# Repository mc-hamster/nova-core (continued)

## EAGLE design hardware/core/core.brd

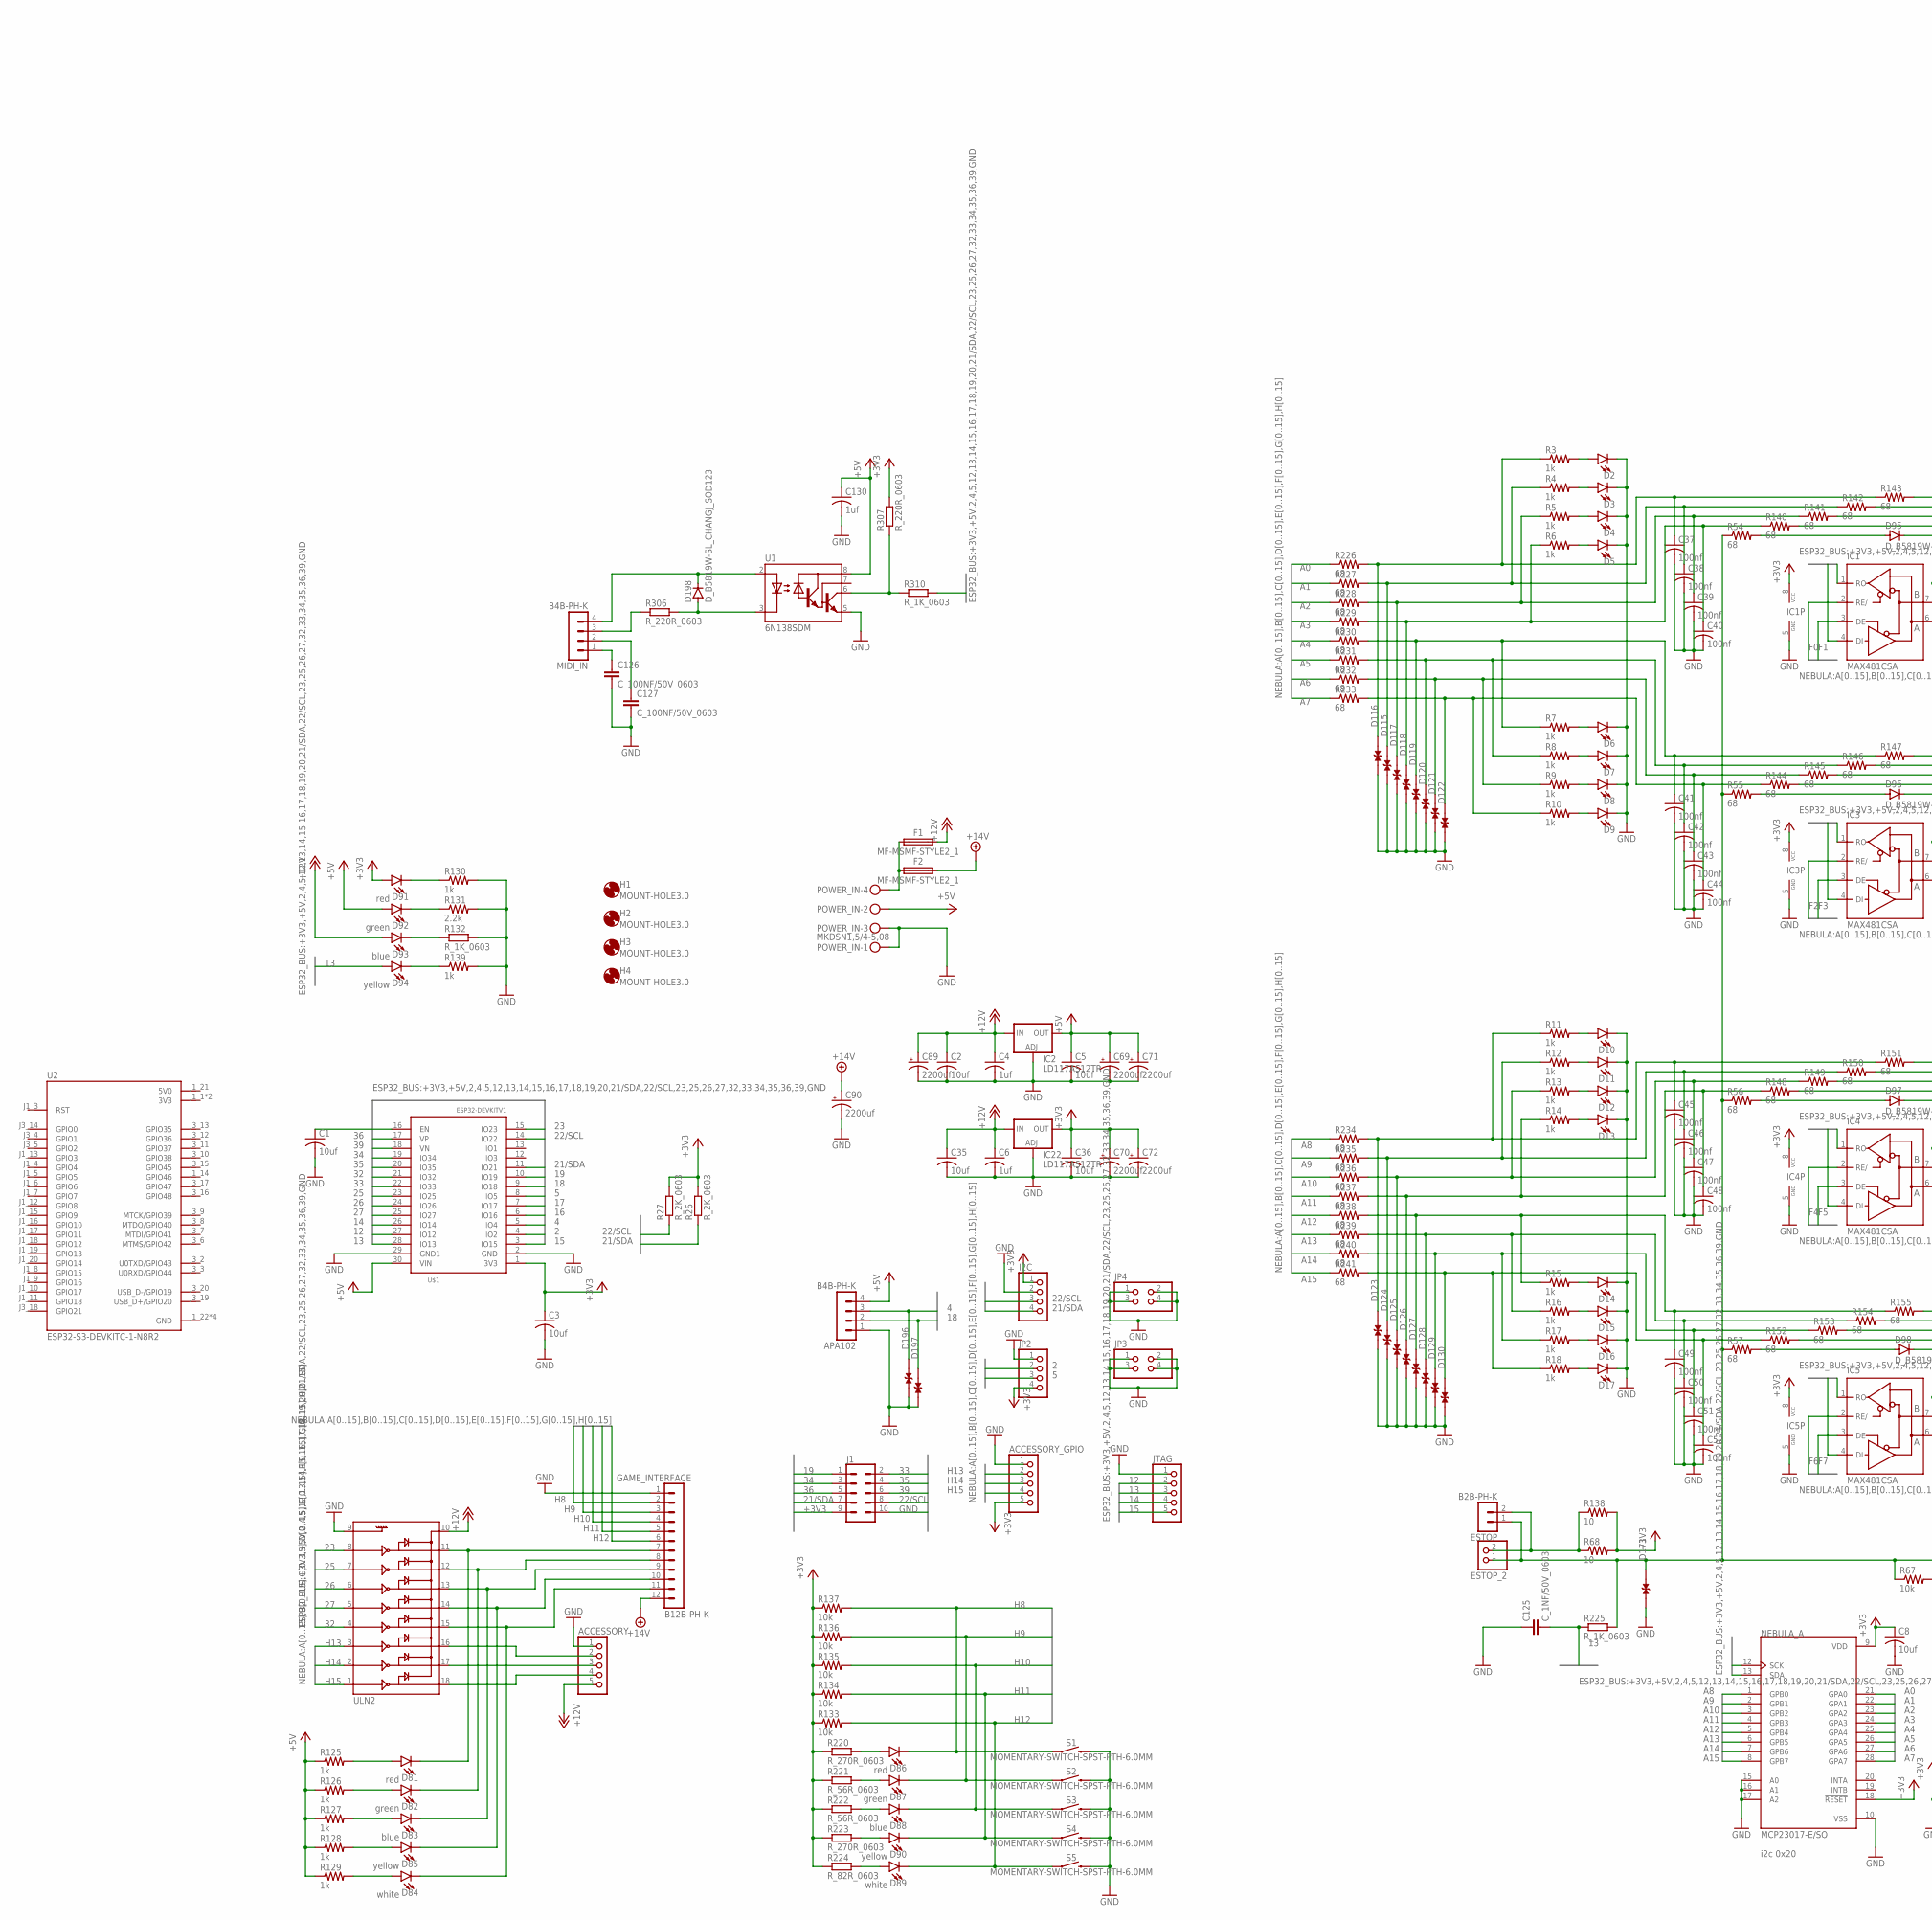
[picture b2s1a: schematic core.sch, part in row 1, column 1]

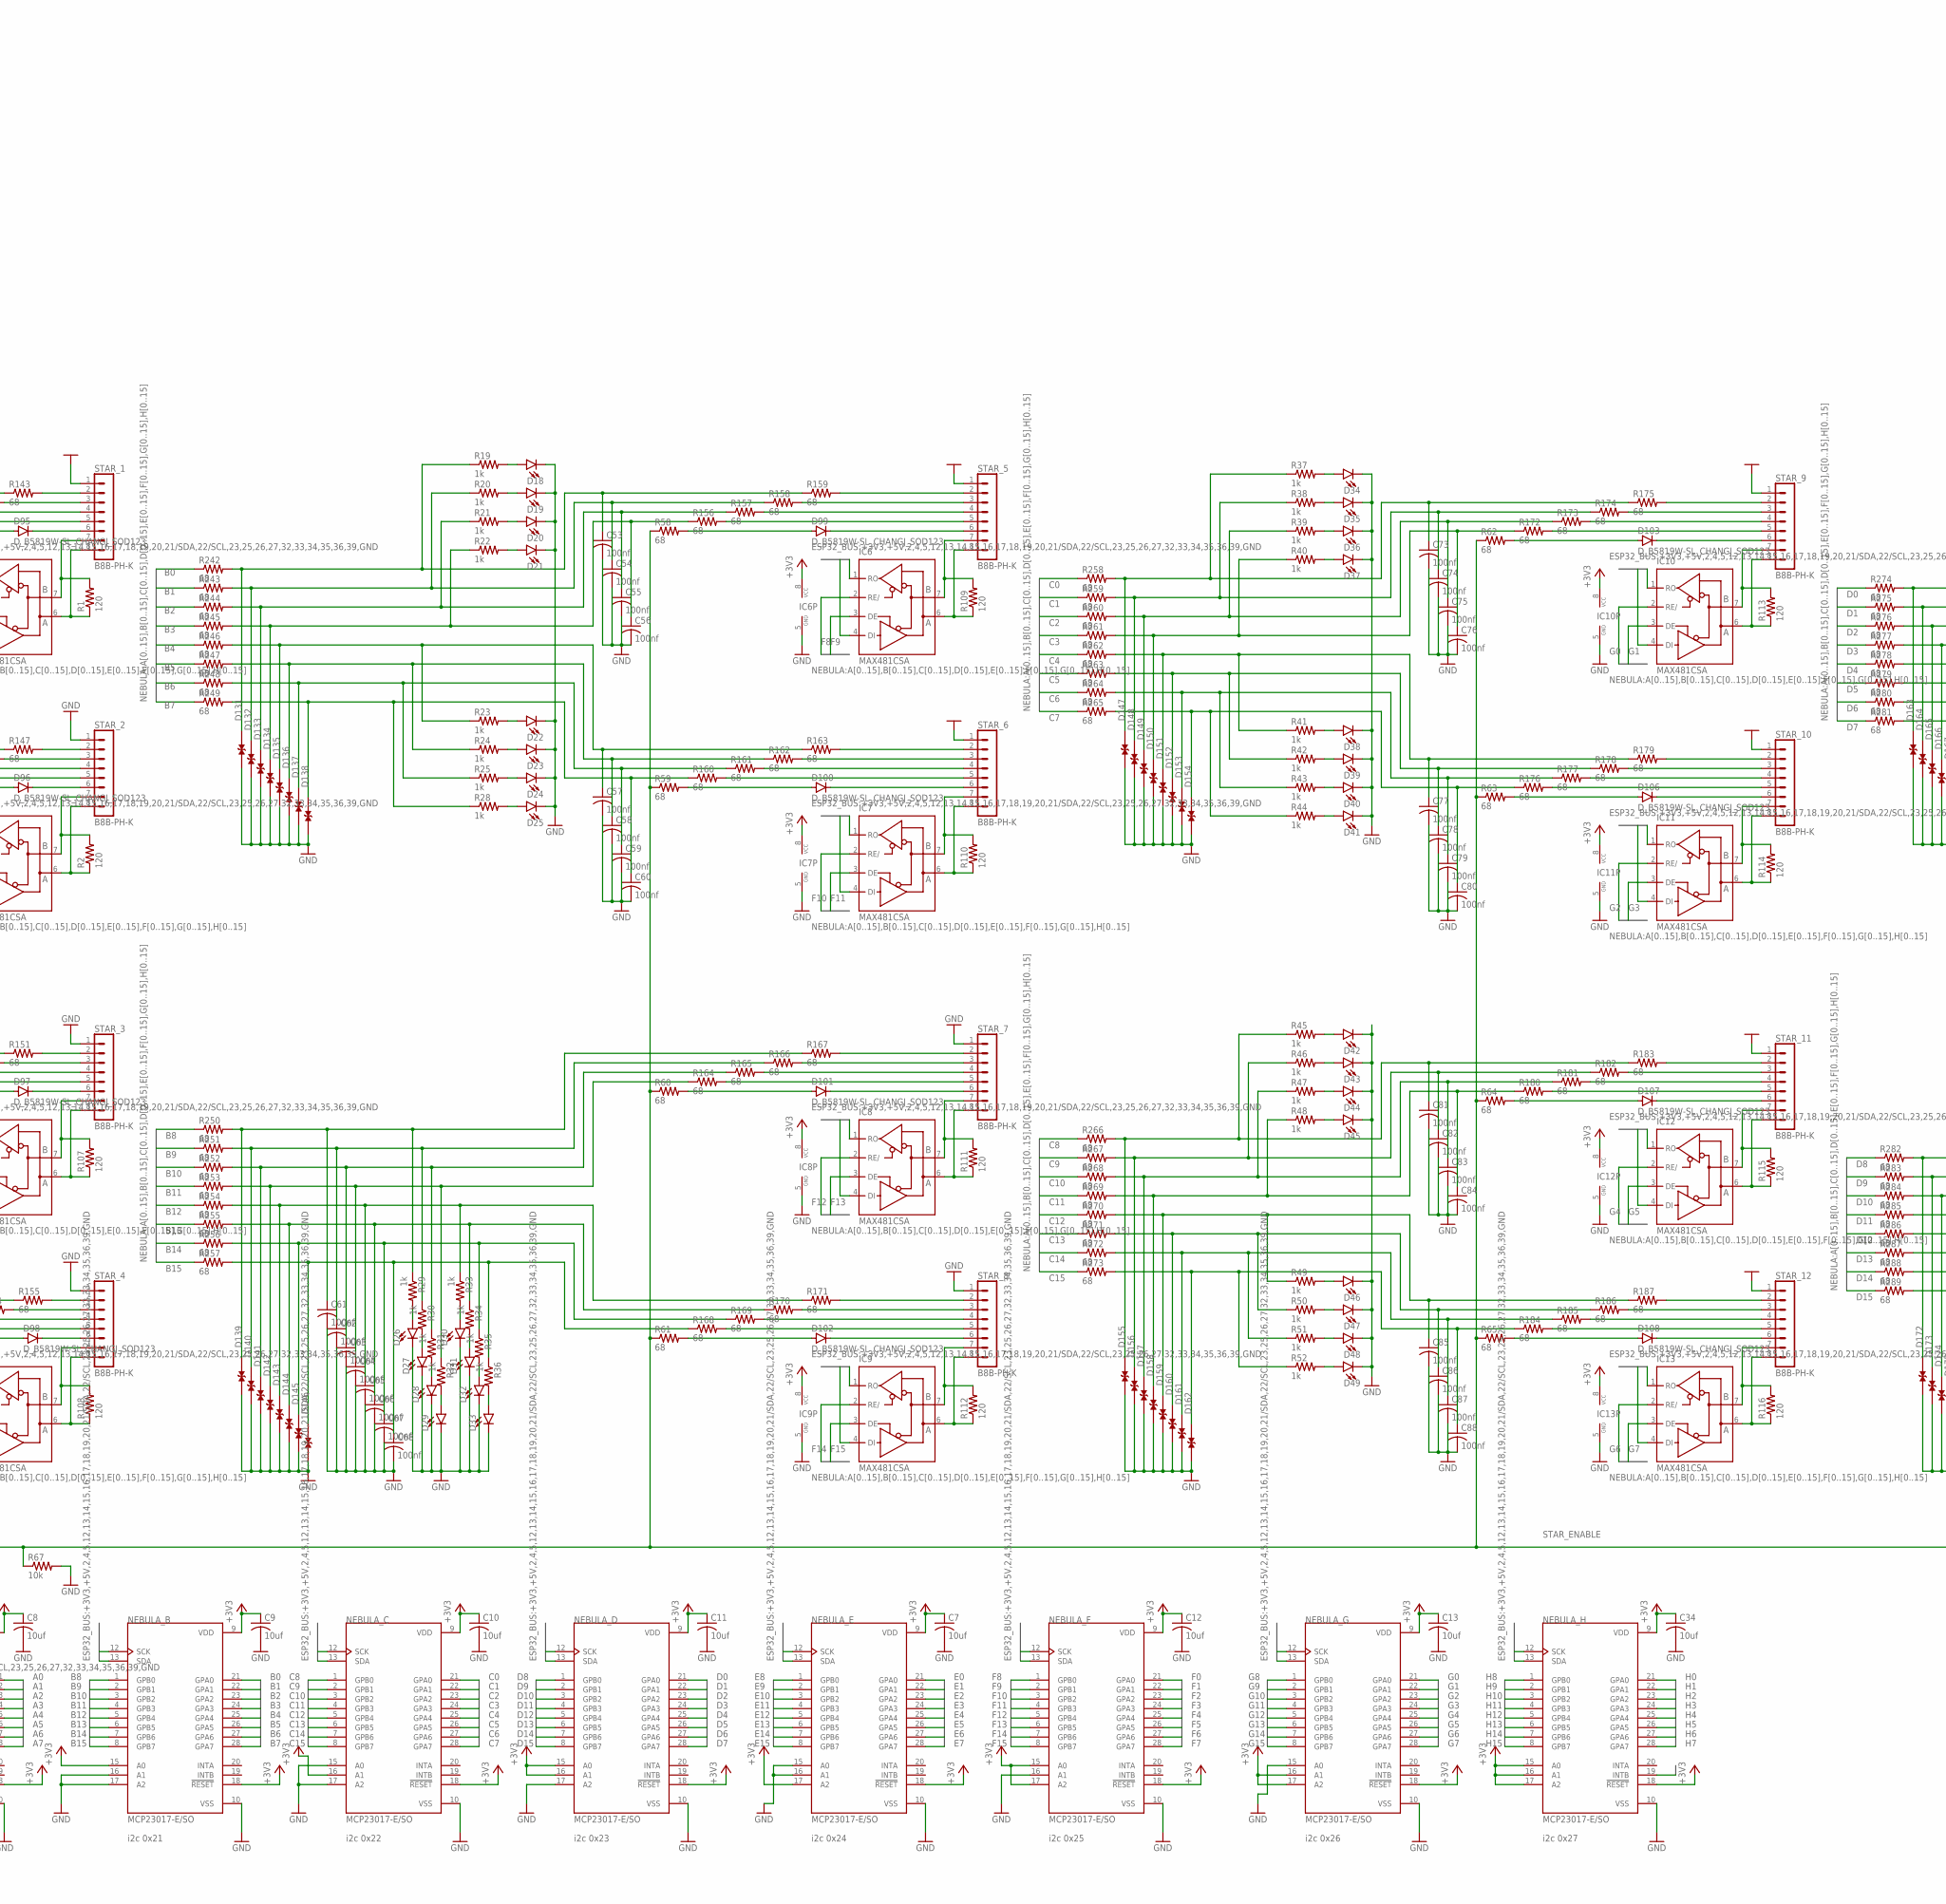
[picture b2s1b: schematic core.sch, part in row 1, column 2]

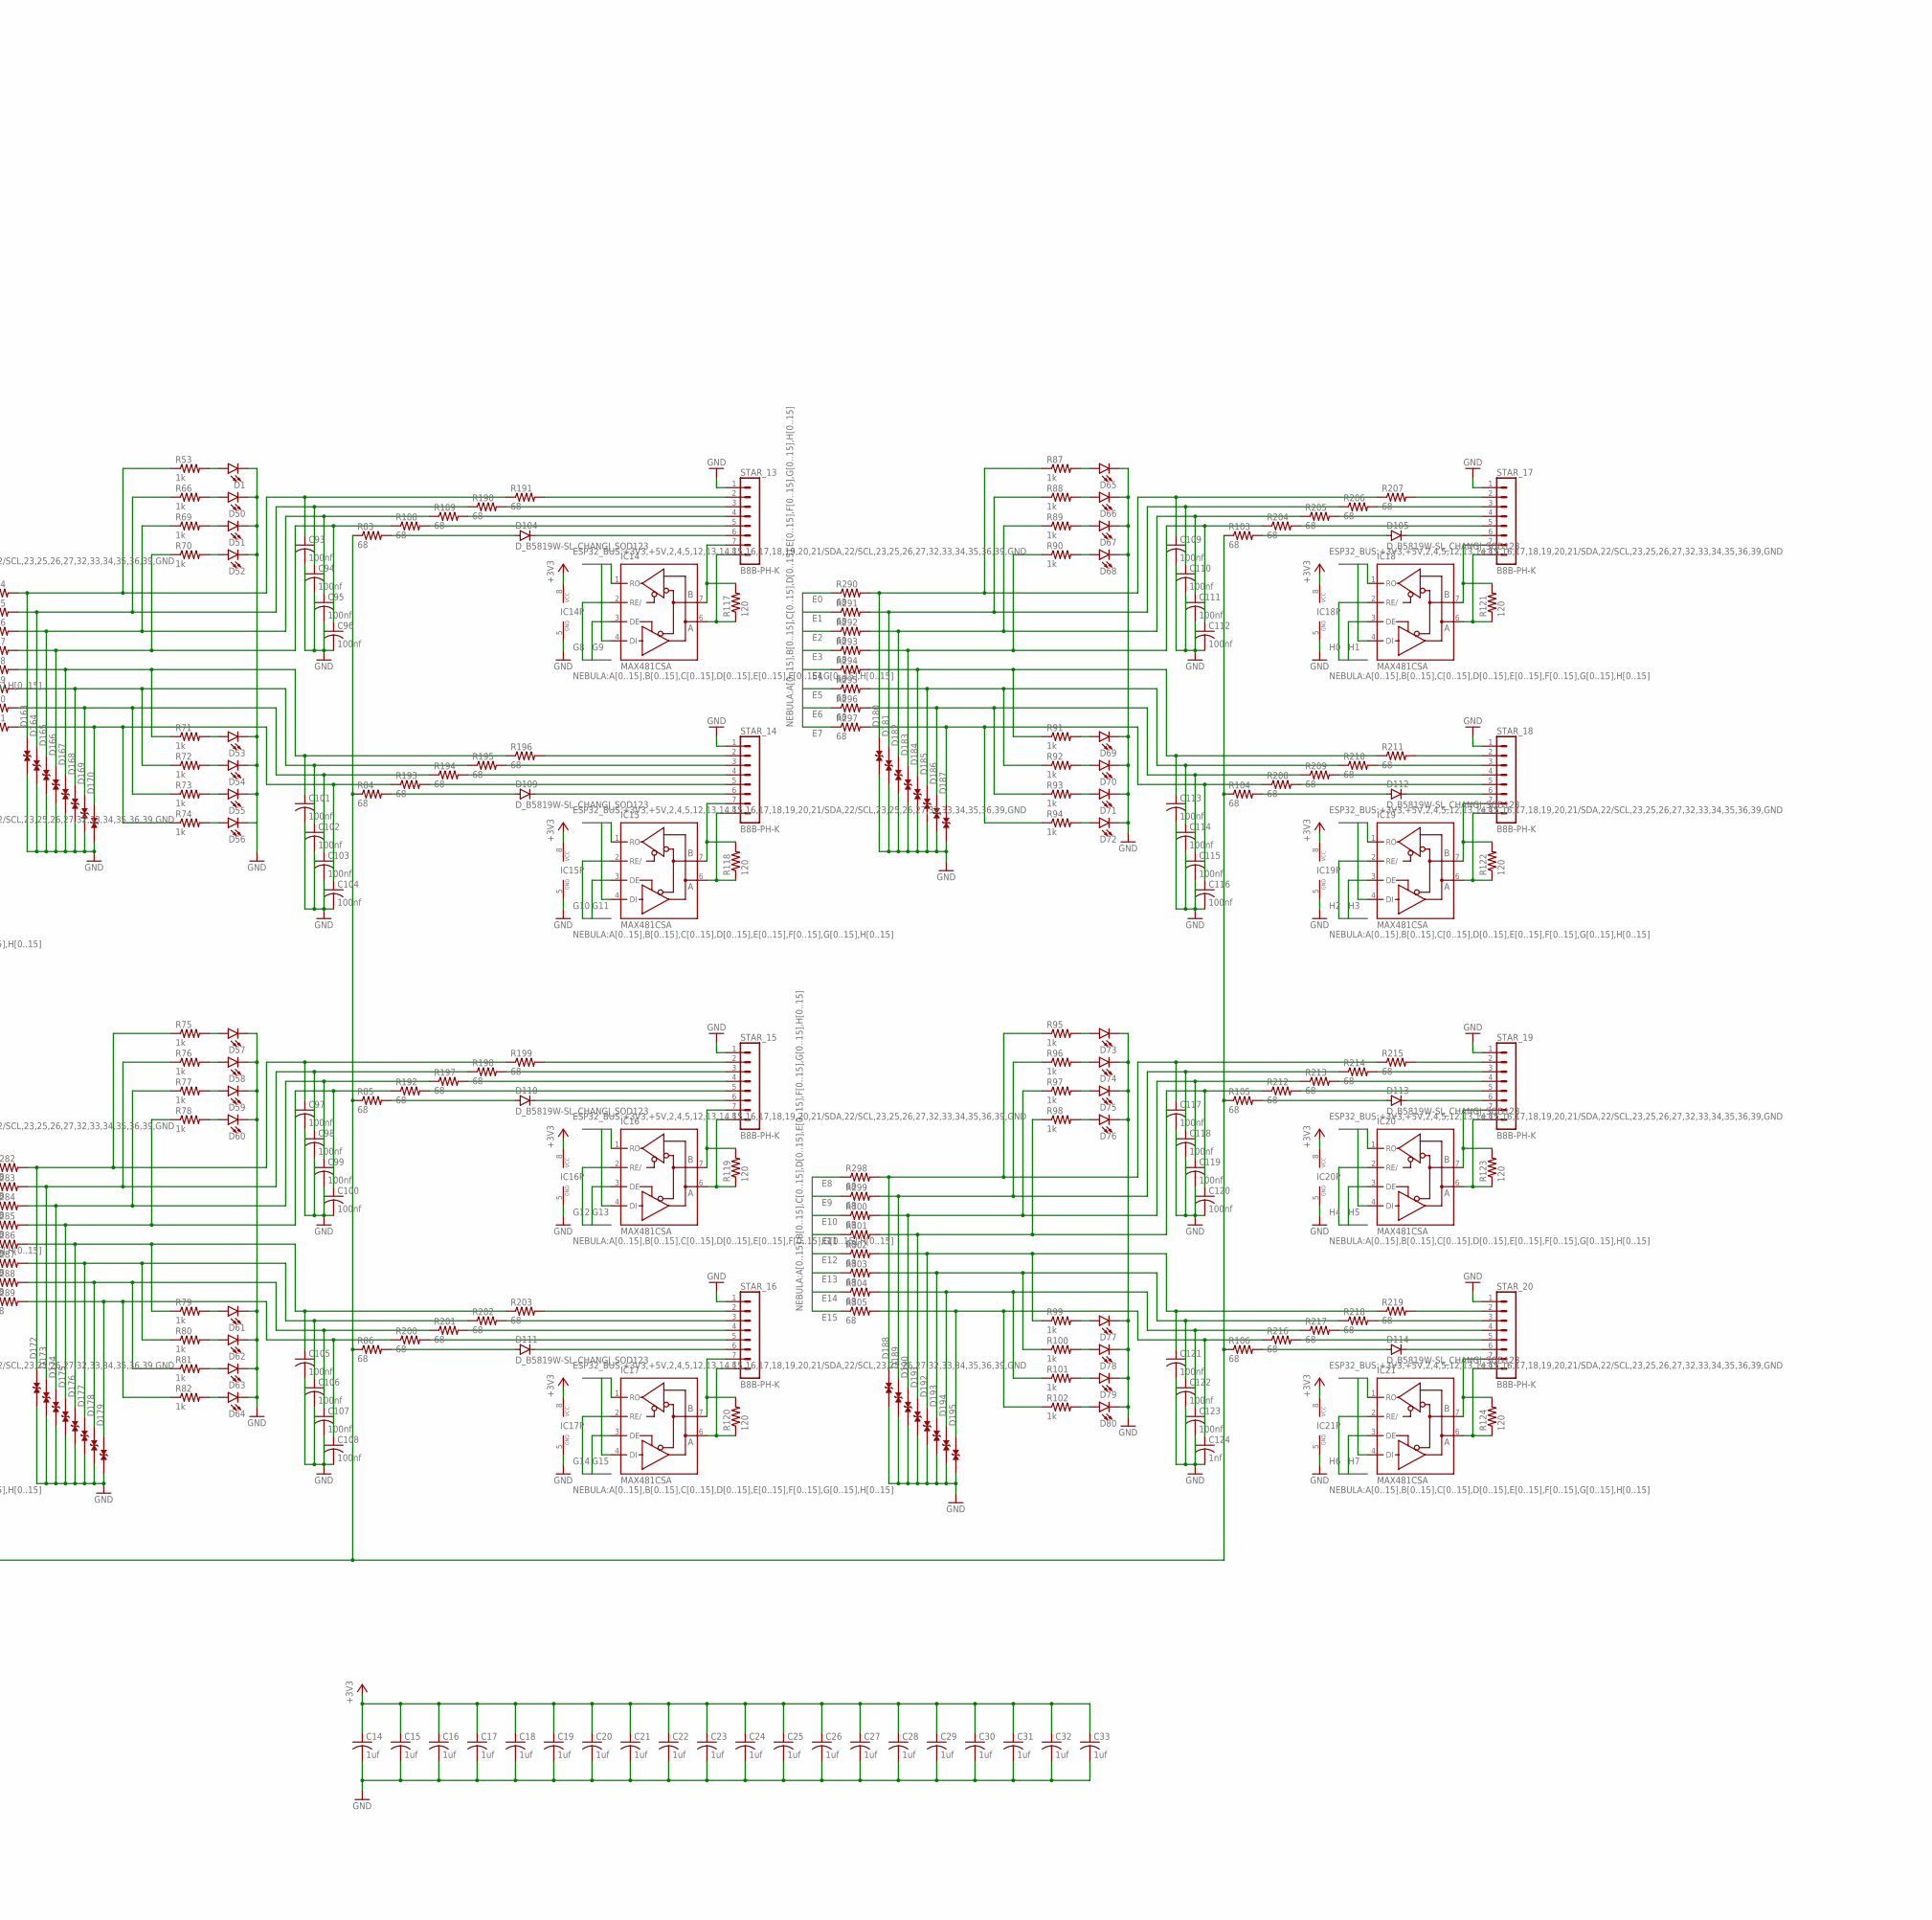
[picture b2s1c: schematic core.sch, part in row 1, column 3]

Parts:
ACCESSORY: PINHD-1X5; 1X05
ACCESSORY_GPIO: PINHD-1X5; 1X05
APA102: B4B-PH-K
C1, C2, C3, C5, C7, C8, C9, C10, C11, C12, C13, C34, C35, C36: 10uf; C0603; LCSC_PART C19702
C4, C6, C14, C15, C16, C17, C18, C19, C20, C21, C22, C23, C24, C25, C26, C27, C28, C29, C30, C31, C32, C33, C130: 1uf; C0805; LCSC_PART C15849
C37, C38, C39, C40, C41, C42, C43, C44, C45, C46, C47, C48, C49, C50, C51, C52, C53, C54, C55, C56, C57, C58, C59, C60, C61, C62, C63, C64, C65, C66, C67, C68, C73, C74, C75, C76, C77, C78, C79, C80, C81, C82, C83, C84, C85, C86, C87, C88, C93, C94, C95, C96, C97, C98, C99, C100, C101, C102, C103, C104, C105, C106, C107, C108, C109, C110, C111, C112, C113, C114, C115, C116, C117, C118, C119, C120, C121, C122, C123: 100nf; C0603; LCSC_PART C14663
C69, C70, C71, C72, C89, C90: 2200uf; E5-13
C124: 1nf; C0603; LCSC_PART C1588
C125: C_1NF/50V_0603; C0603
C126, C127: C_100NF/50V_0603; C0603
D1, D2, D6, D10, D14, D18, D22, D26, D30, D34, D38, D42, D46, D53, D57, D61, D65, D69, D73, D77: LED0603; LED-0603; LCSC_PART C2286
D3, D7, D11, D15, D19, D23, D27, D31, D35, D39, D43, D47, D50, D54, D58, D62, D66, D70, D74, D78: LED0603; LED-0603; LCSC_PART C72043
D4, D8, D12, D16, D20, D24, D28, D32, D36, D40, D44, D48, D51, D55, D59, D63, D67, D71, D75, D79: LED0603; LED-0603; LCSC_PART C72041
D5, D9, D13, D17, D21, D25, D29, D33, D37, D41, D45, D49, D52, D56, D60, D64, D68, D72, D76, D80: LED0603; LED-0603; LCSC_PART C2290
D81, D86, D91: red; LED-0603; LCSC_PART C2286
D82, D87, D92: green; LED-0603; LCSC_PART C72043
D83, D88, D93: blue; LED-0603; LCSC_PART C72041
D84, D89: white; LED-0603; LCSC_PART C2290
D85, D90, D94: yellow; LED-0603; LCSC_PART C72038
D95, D96, D97, D98, D99, D100, D101, D102, D103, D104, D105, D106, D107, D108, D109, D110, D111, D112, D113, D114, D198: D_B5819W-SL_CHANGJ_SOD123; SOD123
D115, D116, D117, D118, D119, D120, D121, D122, D123, D124, D125, D126, D127, D128, D129, D130, D131, D132, D133, D134, D135, D136, D137, D138, D139, D140, D141, D142, D143, D144, D145, D146, D147, D148, D149, D150, D151, D152, D153, D154, D155, D156, D157, D158, D159, D160, D161, D162, D163, D164, D165, D166, D167, D168, D169, D170, D171, D172, D173, D174, D175, D176, D177, D178, D179, D180, D181, D182, D183, D184, D185, D186, D187, D188, D189, D190, D191, D192, D193, D194, D195, D196, D197: SMBJ8.0CA; DIOM4336X265N; LCSC_PART C78757
ESTOP: B2B-PH-K
ESTOP_2: PINHD-1X2; 1X02
F1, F2: MF-MSMF-STYLE2_1; FUSC4632X160; LCSC_PART C78695
GAME_INTERFACE: B12B-PH-K
H1, H2, H3, H4: MOUNT-HOLE3.0; 3,0
I2C: PINHD-1X4; 1X04
IC1, IC3, IC4, IC5, IC6, IC7, IC8, IC9, IC10, IC11, IC12, IC13, IC14, IC15, IC16, IC17, IC18, IC19, IC20, IC21: MAX481CSA; SO08; LCSC_PART C8963
IC2: LD117AS12TR; SOT223; LCSC_PART C6187
IC22: LD117AS12TR; SOT223; LCSC_PART C347222
J1: CONN_05X2SHD; 2X5-SHROUDED
JP2: PINHD-1X4; 1X04
JP3, JP4: PINHD-2X2; 2X02
JTAG: PINHD-1X5; 1X05
MIDI_IN: B4B-PH-K
NEBULA_A: MCP23017-E/SO; SOIC127P1030X265-28N; LCSC_PART C629440
NEBULA_B: MCP23017-E/SO; SOIC127P1030X265-28N; LCSC_PART C629440
NEBULA_C: MCP23017-E/SO; SOIC127P1030X265-28N; LCSC_PART C629440
NEBULA_D: MCP23017-E/SO; SOIC127P1030X265-28N; LCSC_PART C629440
NEBULA_E: MCP23017-E/SO; SOIC127P1030X265-28N; LCSC_PART C629440
NEBULA_F: MCP23017-E/SO; SOIC127P1030X265-28N; LCSC_PART C629440
NEBULA_G: MCP23017-E/SO; SOIC127P1030X265-28N; LCSC_PART C629440
NEBULA_H: MCP23017-E/SO; SOIC127P1030X265-28N; LCSC_PART C629440
POWER_IN: MKDSN1,5/4-5,08
R1, R2, R107, R108, R109, R110, R111, R112, R113, R114, R115, R116, R117, R118, R119, R120, R121, R122, R123, R124: 120; R0603; LCSC_PART C22787
R3, R4, R5, R6, R7, R8, R9, R10, R11, R12, R13, R14, R15, R16, R17, R18, R19, R20, R21, R22, R23, R24, R25, R28, R29, R30, R31, R32, R33, R34, R35, R36, R37, R38, R39, R40, R41, R42, R43, R44, R45, R46, R47, R48, R49, R50, R51, R52, R53, R66, R69, R70, R71, R72, R73, R74, R75, R76, R77, R78, R79, R80, R81, R82, R87, R88, R89, R90, R91, R92, R93, R94, R95, R96, R97, R98, R99, R100, R101, R102, R125, R126, R127, R128, R129, R130, R139: 1k; R0603; LCSC_PART C21190
R26, R27: R_2K_0603; R0603
R54, R55, R56, R57, R58, R59, R60, R61, R62, R63, R64, R65, R83, R84, R85, R86, R103, R104, R105, R106, R140, R141, R142, R143, R144, R145, R146, R147, R148, R149, R150, R151, R152, R153, R154, R155, R156, R157, R158, R159, R160, R161, R162, R163, R164, R165, R166, R167, R168, R169, R170, R171, R172, R173, R174, R175, R176, R177, R178, R179, R180, R181, R182, R183, R184, R185, R186, R187, R188, R189, R190, R191, R192, R193, R194, R195, R196, R197, R198, R199, R200, R201, R202, R203, R204, R205, R206, R207, R208, R209, R210, R211, R212, R213, R214, R215, R216, R217, R218, R219, R226, R227, R228, R229, R230, R231, R232, R233, R234, R235, R236, R237, R238, R239, R240, R241, R242, R243, R244, R245, R246, R247, R248, R249, R250, R251, R252, R253, R254, R255, R256, R257, R258, R259, R260, R261, R262, R263, R264, R265, R266, R267, R268, R269, R270, R271, R272, R273, R274, R275, R276, R277, R278, R279, R280, R281, R282, R283, R284, R285, R286, R287, R288, R289, R290, R291, R292, R293, R294, R295, R296, R297, R298, R299, R300, R301, R302, R303, R304, R305: 68; R0603; LCSC_PART c27592
R67, R133, R134, R135, R136, R137: 10k; R0603; LCSC_PART C25804
R68, R138: 10; R1206; LCSC_PART C17903
R131: 2.2k; R0603; LCSC_PART C4190
R132, R225, R310: R_1K_0603; R0603
R220, R223: R_270R_0603; R0603
R221, R222: R_56R_0603; R0603
R224: R_82R_0603; R0603
R306, R307: R_220R_0603; R0603
S1, S2, S3, S4, S5: MOMENTARY-SWITCH-SPST-PTH-6.0MM; TACTILE_SWITCH_PTH_6.0MM
STAR_1, STAR_2, STAR_3, STAR_4, STAR_5, STAR_6, STAR_7, STAR_8, STAR_9, STAR_10, STAR_11, STAR_12, STAR_13, STAR_14, STAR_15, STAR_16, STAR_17, STAR_18, STAR_19, STAR_20: B8B-PH-K
U1: 6N138SDM; COUPL_6N138SDM; LCSC_PART C188666
U2: ESP32-S3-DEVKITC-1-N8R2; XCVR_ESP32-S3-DEVKITC-1-N8R2
U$1: ESP32DEVKITV1; ESP32-DEVKITV1
ULN2: ULN2803SOICW; SO18L

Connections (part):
2: JP2.2, U$1.4 (IO2)
4: APA102.3, D196.2, U$1.5 (IO4)
5: JP2.3, U$1.8 (IO5)
12: JTAG.2, U$1.27 (IO12)
13: C125.2, D94.A, JTAG.3, R225.1, U$1.28 (IO13)
14: JTAG.4, U$1.26 (IO14)
15: JTAG.5, U$1.3 (IO15)
16/RX2: IC1.1 (RO), IC3.1 (RO), IC4.1 (RO), IC5.1 (RO), IC6.1 (RO), IC7.1 (RO), IC8.1 (RO), IC9.1 (RO), IC10.1 (RO), IC11.1 (RO), IC12.1 (RO), IC13.1 (RO), IC14.1 (RO), IC15.1 (RO), IC16.1 (RO), IC17.1 (RO), IC18.1 (RO), IC19.1 (RO), IC20.1 (RO), IC21.1 (RO), U$1.6 (IO16); also elsewhere on the board
17/TX2: IC1.4 (DI), IC3.4 (DI), IC4.4 (DI), IC5.4 (DI), IC6.4 (DI), IC7.4 (DI), IC8.4 (DI), IC9.4 (DI), IC10.4 (DI), IC11.4 (DI), IC12.4 (DI), IC13.4 (DI), IC14.4 (DI), IC15.4 (DI), IC16.4 (DI), IC17.4 (DI), IC18.4 (DI), IC19.4 (DI), IC20.4 (DI), IC21.4 (DI), U$1.7 (IO17); also elsewhere on the board
18: APA102.2, D197.2, U$1.9 (IO18)
19: J1.1, R307.1, R310.1, R310.2, U1.6 (VO), U$1.10 (IO19)
21/SDA: I2C.4, J1.7, NEBULA_A.13 (SDA), NEBULA_B.13 (SDA), NEBULA_C.13 (SDA), NEBULA_D.13 (SDA), NEBULA_E.13 (SDA), NEBULA_F.13 (SDA), NEBULA_G.13 (SDA), NEBULA_H.13 (SDA), R26.1, U$1.11 (IO21)
22/SCL: I2C.3, J1.8, NEBULA_A.12 (SCK), NEBULA_B.12 (SCK), NEBULA_C.12 (SCK), NEBULA_D.12 (SCK), NEBULA_E.12 (SCK), NEBULA_F.12 (SCK), NEBULA_G.12 (SCK), NEBULA_H.12 (SCK), R27.1, U$1.14 (IO22)
23: U$1.15 (IO23), ULN2.8
25: U$1.23 (IO25), ULN2.7
26: U$1.24 (IO26), ULN2.6
27: U$1.25 (IO27), ULN2.5
32: U$1.21 (IO32), ULN2.4
33: J1.2, U$1.22 (IO33)
34: J1.3, U$1.19 (IO34)
35: J1.4, U$1.20 (IO35)
36: J1.5, U$1.17 (VP)
39: J1.6, NEBULA_H.19 (INTB), U$1.18 (VN)
+3V3: ACCESSORY_GPIO.5, C3.1, C7.1, C8.1, C9.1, C10.1, C11.1, C12.1, C13.1, C14.1, C15.1, C16.1, C17.1, C18.1, C19.1, C20.1, C21.1, C22.1, C23.1, C24.1, C25.1, C26.1, C27.1, C28.1, C29.1, C30.1, C31.1, C32.1, C33.1, C34.1, C36.1, C70.+, C72.+, D91.A, I2C.1, IC1.8 (VCC), IC3.8 (VCC), IC4.8 (VCC), IC5.8 (VCC), IC6.8 (VCC), IC7.8 (VCC), IC8.8 (VCC), IC9.8 (VCC), IC10.8 (VCC), IC11.8 (VCC), IC12.8 (VCC), IC13.8 (VCC), IC14.8 (VCC), IC15.8 (VCC), IC16.8 (VCC), IC17.8 (VCC), IC18.8 (VCC), IC19.8 (VCC), IC20.8 (VCC), IC21.8 (VCC), IC22.4 (OUT), J1.9, JP2.4, NEBULA_A.9 (VDD), NEBULA_A.18 (!RESET), NEBULA_B.9 (VDD), NEBULA_B.15 (A0), NEBULA_B.18 (!RESET), NEBULA_C.9 (VDD), NEBULA_C.16 (A1), NEBULA_C.18 (!RESET), NEBULA_D.9 (VDD), NEBULA_D.15 (A0), NEBULA_D.16 (A1), NEBULA_D.18 (!RESET), NEBULA_E.9 (VDD), NEBULA_E.17 (A2), NEBULA_E.18 (!RESET), NEBULA_F.9 (VDD), NEBULA_F.15 (A0), NEBULA_F.17 (A2), NEBULA_F.18 (!RESET), NEBULA_G.9 (VDD), NEBULA_G.16 (A1), NEBULA_G.17 (A2)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
+5V: APA102.4, C5.1, C69.+, C71.+, C130.1, D92.A, IC2.4 (OUT), POWER_IN.2, R125.1, R126.1, R127.1, R128.1, R129.1, U1.8 (VCC), U$1.30 (VIN)
+12V: ACCESSORY.5, C2.1, C4.1, C6.1, C35.1, C89.+, D93.A, F1.2, IC2.3 (IN), IC22.3 (IN), ULN2.10
+14V: C90.+, F2.2, GAME_INTERFACE.12
A0: NEBULA_A.21 (GPA0), R226.1
A1: NEBULA_A.22 (GPA1), R227.1
A2: NEBULA_A.23 (GPA2), R228.1
A3: NEBULA_A.24 (GPA3), R229.1
A4: NEBULA_A.25 (GPA4), R230.1
A5: NEBULA_A.26 (GPA5), R231.1
A6: NEBULA_A.27 (GPA6), R232.1
A7: NEBULA_A.28 (GPA7), R233.1
A8: NEBULA_A.1 (GPB0), R234.1
A9: NEBULA_A.2 (GPB1), R235.1
A10: NEBULA_A.3 (GPB2), R236.1
A11: NEBULA_A.4 (GPB3), R237.1
A12: NEBULA_A.5 (GPB4), R238.1
A13: NEBULA_A.6 (GPB5), R239.1
A14: NEBULA_A.7 (GPB6), R240.1
A15: NEBULA_A.8 (GPB7), R241.1
B0: NEBULA_B.21 (GPA0), R242.1
B1: NEBULA_B.22 (GPA1), R243.1
B2: NEBULA_B.23 (GPA2), R244.1
B3: NEBULA_B.24 (GPA3), R245.1
B4: NEBULA_B.25 (GPA4), R246.1
B5: NEBULA_B.26 (GPA5), R247.1
B6: NEBULA_B.27 (GPA6), R248.1
B7: NEBULA_B.28 (GPA7), R249.1
B8: NEBULA_B.1 (GPB0), R250.1
B9: NEBULA_B.2 (GPB1), R251.1
B10: NEBULA_B.3 (GPB2), R252.1
B11: NEBULA_B.4 (GPB3), R253.1
B12: NEBULA_B.5 (GPB4), R254.1
B13: NEBULA_B.6 (GPB5), R255.1
B14: NEBULA_B.7 (GPB6), R256.1
B15: NEBULA_B.8 (GPB7), R257.1
C0: NEBULA_C.21 (GPA0), R258.1
C1: NEBULA_C.22 (GPA1), R259.1
C2: NEBULA_C.23 (GPA2), R260.1
C3: NEBULA_C.24 (GPA3), R261.1
C4: NEBULA_C.25 (GPA4), R262.1
C5: NEBULA_C.26 (GPA5), R263.1
C6: NEBULA_C.27 (GPA6), R264.1
C7: NEBULA_C.28 (GPA7), R265.1
C8: NEBULA_C.1 (GPB0), R266.1
C9: NEBULA_C.2 (GPB1), R267.1
C10: NEBULA_C.3 (GPB2), R268.1
C11: NEBULA_C.4 (GPB3), R269.1
C12: NEBULA_C.5 (GPB4), R270.1
C13: NEBULA_C.6 (GPB5), R271.1
C14: NEBULA_C.7 (GPB6), R272.1
C15: NEBULA_C.8 (GPB7), R273.1
D0: NEBULA_D.21 (GPA0), R274.1
D1: NEBULA_D.22 (GPA1), R275.1
D2: NEBULA_D.23 (GPA2), R276.1
D3: NEBULA_D.24 (GPA3), R277.1
D4: NEBULA_D.25 (GPA4), R278.1
D5: NEBULA_D.26 (GPA5), R279.1
D6: NEBULA_D.27 (GPA6), R280.1
D7: NEBULA_D.28 (GPA7), R281.1
D8: NEBULA_D.1 (GPB0), R282.1
D9: NEBULA_D.2 (GPB1), R283.1
D10: NEBULA_D.3 (GPB2), R284.1
D11: NEBULA_D.4 (GPB3), R285.1
D12: NEBULA_D.5 (GPB4), R286.1
D13: NEBULA_D.6 (GPB5), R287.1
D14: NEBULA_D.7 (GPB6), R288.1
D15: NEBULA_D.8 (GPB7), R289.1
E0: NEBULA_E.21 (GPA0), R290.1
E1: NEBULA_E.22 (GPA1), R291.1
E2: NEBULA_E.23 (GPA2), R292.1
E3: NEBULA_E.24 (GPA3), R293.1
E4: NEBULA_E.25 (GPA4), R294.1
E5: NEBULA_E.26 (GPA5), R295.1
E6: NEBULA_E.27 (GPA6), R296.1
E7: NEBULA_E.28 (GPA7), R297.1
E8: NEBULA_E.1 (GPB0), R298.1
E9: NEBULA_E.2 (GPB1), R299.1
E10: NEBULA_E.3 (GPB2), R300.1
E11: NEBULA_E.4 (GPB3), R301.1
E12: NEBULA_E.5 (GPB4), R302.1
E13: NEBULA_E.6 (GPB5), R303.1
E14: NEBULA_E.7 (GPB6), R304.1
E15: NEBULA_E.8 (GPB7), R305.1
F0: IC1.2 (RE/), NEBULA_F.21 (GPA0); also elsewhere on the board
F1: IC1.3 (DE), NEBULA_F.22 (GPA1); also elsewhere on the board
F2: IC3.2 (RE/), NEBULA_F.23 (GPA2); also elsewhere on the board
F3: IC3.3 (DE), NEBULA_F.24 (GPA3); also elsewhere on the board
F4: IC4.2 (RE/), NEBULA_F.25 (GPA4); also elsewhere on the board
F5: IC4.3 (DE), NEBULA_F.26 (GPA5); also elsewhere on the board
F6: IC5.2 (RE/), NEBULA_F.27 (GPA6); also elsewhere on the board
F7: IC5.3 (DE), NEBULA_F.28 (GPA7); also elsewhere on the board
F8: IC6.2 (RE/), NEBULA_F.1 (GPB0); also elsewhere on the board
F9: IC6.3 (DE), NEBULA_F.2 (GPB1); also elsewhere on the board
F10: IC7.2 (RE/), NEBULA_F.3 (GPB2); also elsewhere on the board
F11: IC7.3 (DE), NEBULA_F.4 (GPB3); also elsewhere on the board
F12: IC8.2 (RE/), NEBULA_F.5 (GPB4); also elsewhere on the board
F13: IC8.3 (DE), NEBULA_F.6 (GPB5); also elsewhere on the board
F14: IC9.2 (RE/), NEBULA_F.7 (GPB6); also elsewhere on the board
F15: IC9.3 (DE), NEBULA_F.8 (GPB7); also elsewhere on the board
G0: IC10.2 (RE/), NEBULA_G.21 (GPA0); also elsewhere on the board
G1: IC10.3 (DE), NEBULA_G.22 (GPA1); also elsewhere on the board
G2: IC11.2 (RE/), NEBULA_G.23 (GPA2); also elsewhere on the board
G3: IC11.3 (DE), NEBULA_G.24 (GPA3); also elsewhere on the board
G4: IC12.2 (RE/), NEBULA_G.25 (GPA4); also elsewhere on the board
G5: IC12.3 (DE), NEBULA_G.26 (GPA5); also elsewhere on the board
G6: IC13.2 (RE/), NEBULA_G.27 (GPA6); also elsewhere on the board
G7: IC13.3 (DE), NEBULA_G.28 (GPA7); also elsewhere on the board
G8: IC14.2 (RE/), NEBULA_G.1 (GPB0); also elsewhere on the board
G9: IC14.3 (DE), NEBULA_G.2 (GPB1); also elsewhere on the board
G10: IC15.2 (RE/), NEBULA_G.3 (GPB2); also elsewhere on the board
G11: IC15.3 (DE), NEBULA_G.4 (GPB3); also elsewhere on the board
G12: IC16.2 (RE/), NEBULA_G.5 (GPB4); also elsewhere on the board
G13: IC16.3 (DE), NEBULA_G.6 (GPB5); also elsewhere on the board
G14: IC17.2 (RE/), NEBULA_G.7 (GPB6); also elsewhere on the board
G15: IC17.3 (DE), NEBULA_G.8 (GPB7); also elsewhere on the board
GND: ACCESSORY.1, ACCESSORY_GPIO.1, APA102.1, C1.2, C2.2, C3.2, C4.2, C5.2, C6.2, C7.2, C8.2, C9.2, C10.2, C11.2, C12.2, C13.2, C14.2, C15.2, C16.2, C17.2, C18.2, C19.2, C20.2, C21.2, C22.2, C23.2, C24.2, C25.2, C26.2, C27.2, C28.2, C29.2, C30.2, C31.2, C32.2, C33.2, C34.2, C35.2, C36.2, C37.2, C38.2, C39.2, C40.2, C41.2, C42.2, C43.2, C44.2, C45.2, C46.2, C47.2, C48.2, C49.2, C50.2, C51.2, C52.2, C53.2, C54.2, C55.2, C56.2, C57.2, C58.2, C59.2, C60.2, C61.2, C62.2, C63.2, C64.2, C65.2, C66.2, C67.2, C68.2, C69.-, C70.-, C71.-, C72.-, C73.2, C74.2, C75.2, C76.2, C77.2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; also elsewhere on the board
H0: IC18.2 (RE/), NEBULA_H.21 (GPA0); also elsewhere on the board
H1: IC18.3 (DE), NEBULA_H.22 (GPA1); also elsewhere on the board
H2: IC19.2 (RE/), NEBULA_H.23 (GPA2); also elsewhere on the board
H3: IC19.3 (DE), NEBULA_H.24 (GPA3); also elsewhere on the board
H4: IC20.2 (RE/), NEBULA_H.25 (GPA4); also elsewhere on the board
H5: IC20.3 (DE), NEBULA_H.26 (GPA5); also elsewhere on the board
H6: IC21.2 (RE/), NEBULA_H.27 (GPA6); also elsewhere on the board
H7: IC21.3 (DE), NEBULA_H.28 (GPA7); also elsewhere on the board
H8: D86.C, GAME_INTERFACE.2, NEBULA_H.1 (GPB0), R137.2, S1.1
H9: D87.C, GAME_INTERFACE.3, NEBULA_H.2 (GPB1), R136.2, S2.1
H10: D88.C, GAME_INTERFACE.4, NEBULA_H.3 (GPB2), R135.2, S3.1
H11: D90.C, GAME_INTERFACE.5, NEBULA_H.4 (GPB3), R134.2, S4.1
H12: D89.C, GAME_INTERFACE.6, NEBULA_H.5 (GPB4), R133.2, S5.1
H13: ACCESSORY_GPIO.2, NEBULA_H.6 (GPB5), ULN2.3
H14: ACCESSORY_GPIO.3, NEBULA_H.7 (GPB6), ULN2.2
H15: ACCESSORY_GPIO.4, NEBULA_H.8 (GPB7), ULN2.1
unnamed: C1.1, U$1.16 (EN)
unnamed: D98.A, R57.2
unnamed: D2.A, R3.2
unnamed: D3.A, R4.2
unnamed: D4.A, R5.2
unnamed: D5.A, R6.2
unnamed: D98.C, STAR_4.6
unnamed: D97.A, R56.2
unnamed: D95.A, R54.2
unnamed: D102.A, R61.2
unnamed: D6.A, R7.2
unnamed: D7.A, R8.2
unnamed: D8.A, R9.2
unnamed: D9.A, R10.2
unnamed: D102.C, STAR_8.6
unnamed: D101.A, R60.2
unnamed: D101.C, STAR_7.6
unnamed: D103.A, R62.2
unnamed: D103.C, STAR_9.6
unnamed: D14.A, R15.2
unnamed: D15.A, R16.2
unnamed: D16.A, R17.2
unnamed: D17.A, R18.2
unnamed: D104.A, R83.2
unnamed: D104.C, STAR_13.6
unnamed: D56.A, R74.2
unnamed: D55.A, R73.2
unnamed: D13.A, R14.2
unnamed: D12.A, R13.2
unnamed: D11.A, R12.2
unnamed: D10.A, R11.2
unnamed: D54.A, R72.2
unnamed: D53.A, R71.2
unnamed: D80.A, R102.2
unnamed: D1.A, R53.2
unnamed: D25.A, R28.2
unnamed: D24.A, R25.2
unnamed: D23.A, R24.2
unnamed: D22.A, R23.2
unnamed: D50.A, R66.2
unnamed: D51.A, R69.2
unnamed: D52.A, R70.2
unnamed: D61.A, R79.2
unnamed: D21.A, R22.2
unnamed: D20.A, R21.2
unnamed: D19.A, R20.2
unnamed: D18.A, R19.2
unnamed: D62.A, R80.2
unnamed: D63.A, R81.2
unnamed: D64.A, R82.2
unnamed: D81.C, GAME_INTERFACE.7, ULN2.11
unnamed: D26.A, R29.2
unnamed: D27.A, R30.2
unnamed: D28.A, R31.2
unnamed: D29.A, R32.2
unnamed: D82.C, GAME_INTERFACE.8, ULN2.12
unnamed: D83.C, GAME_INTERFACE.9, ULN2.13
unnamed: D85.C, GAME_INTERFACE.10, ULN2.14
unnamed: D84.C, GAME_INTERFACE.11, ULN2.15
unnamed: D30.A, R33.2
unnamed: D31.A, R34.2
unnamed: D32.A, R35.2
unnamed: D33.A, R36.2
unnamed: D57.A, R75.2
unnamed: D58.A, R76.2
unnamed: D59.A, R77.2
unnamed: D60.A, R78.2
unnamed: D34.A, R37.2
unnamed: D35.A, R38.2
unnamed: D36.A, R39.2
unnamed: D37.A, R40.2
unnamed: D106.A, R63.2
unnamed: D106.C, STAR_10.6
unnamed: D107.A, R64.2
unnamed: D107.C, STAR_11.6
unnamed: D38.A, R41.2
unnamed: D39.A, R42.2
unnamed: D40.A, R43.2
unnamed: D41.A, R44.2
unnamed: D79.A, R101.2
unnamed: D78.A, R100.2
unnamed: D77.A, R99.2
unnamed: D76.A, R98.2
unnamed: D42.A, R45.2
unnamed: D43.A, R46.2
unnamed: D44.A, R47.2
unnamed: D75.A, R97.2
unnamed: ESTOP.2, ESTOP_2.2, R68.1, R138.1
unnamed: D74.A, R96.2
unnamed: D73.A, R95.2
unnamed: D65.A, R87.2
unnamed: D45.A, R48.2
unnamed: D46.A, R49.2
unnamed: D47.A, R50.2
unnamed: D48.A, R51.2
unnamed: D66.A, R88.2
unnamed: D67.A, R89.2
unnamed: D68.A, R90.2
unnamed: D69.A, R91.2
unnamed: D70.A, R92.2
unnamed: D71.A, R93.2
unnamed: D72.A, R94.2
unnamed: D108.A, R65.2
unnamed: D108.C, STAR_12.6
unnamed: D111.A, R86.2
unnamed: D111.C, STAR_16.6
unnamed: IC1.7 (B), R1.2, STAR_1.7
unnamed: IC1.6 (A), R1.1, STAR_1.8
unnamed: IC3.7 (B), R2.2, STAR_2.7
unnamed: IC3.6 (A), R2.1, STAR_2.8
unnamed: IC4.7 (B), R107.2, STAR_3.7
unnamed: IC4.6 (A), R107.1, STAR_3.8
unnamed: IC5.7 (B), R108.2, STAR_4.7
unnamed: IC5.6 (A), R108.1, STAR_4.8
unnamed: IC6.7 (B), R109.2, STAR_5.7
unnamed: IC6.6 (A), R109.1, STAR_5.8
unnamed: IC7.7 (B), R110.2, STAR_6.7
unnamed: IC7.6 (A), R110.1, STAR_6.8
unnamed: IC8.7 (B), R111.2, STAR_7.7
unnamed: IC8.6 (A), R111.1, STAR_7.8
unnamed: IC9.7 (B), R112.2, STAR_8.7
unnamed: IC9.6 (A), R112.1, STAR_8.8
unnamed: IC10.7 (B), R113.2, STAR_9.7
unnamed: IC10.6 (A), R113.1, STAR_9.8
unnamed: IC11.7 (B), R114.2, STAR_10.7
unnamed: IC11.6 (A), R114.1, STAR_10.8
unnamed: IC12.7 (B), R115.2, STAR_11.7
unnamed: IC12.6 (A), R115.1, STAR_11.8
unnamed: IC13.7 (B), R116.2, STAR_12.7
unnamed: IC13.6 (A), R116.1, STAR_12.8
unnamed: IC14.7 (B), R117.2, STAR_13.7
unnamed: IC14.6 (A), R117.1, STAR_13.8
unnamed: IC15.7 (B), R118.2, STAR_14.7
unnamed: IC15.6 (A), R118.1, STAR_14.8
unnamed: IC16.7 (B), R119.2, STAR_15.7
unnamed: IC16.6 (A), R119.1, STAR_15.8
unnamed: IC17.7 (B), R120.2, STAR_16.7
unnamed: IC17.6 (A), R120.1, STAR_16.8
unnamed: IC18.7 (B), R121.2, STAR_17.7
unnamed: IC18.6 (A), R121.1, STAR_17.8
unnamed: IC19.7 (B), R122.2, STAR_18.7
unnamed: IC19.6 (A), R122.1, STAR_18.8
unnamed: IC20.7 (B), R123.2, STAR_19.7
unnamed: IC20.6 (A), R123.1, STAR_19.8
unnamed: IC21.7 (B), R124.2, STAR_20.7
unnamed: IC21.6 (A), R124.1, STAR_20.8
unnamed: ACCESSORY.2, ULN2.16
unnamed: ACCESSORY.3, ULN2.17
unnamed: ACCESSORY.4, ULN2.18
unnamed: D84.A, R129.2
unnamed: D85.A, R128.2
unnamed: D83.A, R127.2
unnamed: D82.A, R126.2
unnamed: D81.A, R125.2
unnamed: D91.C, R130.1
unnamed: D92.C, R131.1
unnamed: D93.C, R132.1
unnamed: D94.C, R139.1
unnamed: C37.1, D116.2, R3.1, R143.1, R226.2
unnamed: C38.1, D115.2, R4.1, R142.1, R227.2
unnamed: C39.1, D117.2, R5.1, R141.1, R228.2
unnamed: C40.1, D118.2, R6.1, R140.1, R229.2
unnamed: C44.1, D122.2, R10.1, R144.1, R233.2
unnamed: C43.1, D121.2, R9.1, R145.1, R232.2
unnamed: C42.1, D120.2, R8.1, R146.1, R231.2
unnamed: C41.1, D119.2, R7.1, R147.1, R230.2
unnamed: R143.2, STAR_1.2
unnamed: R142.2, STAR_1.3
unnamed: R141.2, STAR_1.4
unnamed: R140.2, STAR_1.5
unnamed: R147.2, STAR_2.2
unnamed: R146.2, STAR_2.3
unnamed: R145.2, STAR_2.4
unnamed: R144.2, STAR_2.5
unnamed: R151.2, STAR_3.2
unnamed: R150.2, STAR_3.3
unnamed: R149.2, STAR_3.4
unnamed: R148.2, STAR_3.5
unnamed: R155.2, STAR_4.2
unnamed: R154.2, STAR_4.3
unnamed: R153.2, STAR_4.4
unnamed: R152.2, STAR_4.5
unnamed: D49.A, R52.2
unnamed: C46.1, D124.2, R12.1, R150.1, R235.2
unnamed: C47.1, D125.2, R13.1, R149.1, R236.2
unnamed: C48.1, D126.2, R14.1, R148.1, R237.2
unnamed: C52.1, D130.2, R18.1, R152.1, R241.2
unnamed: C51.1, D129.2, R17.1, R153.1, R240.2
unnamed: C50.1, D128.2, R16.1, R154.1, R239.2
unnamed: C49.1, D127.2, R15.1, R155.1, R238.2
unnamed: C53.1, D131.2, R19.1, R159.1, R242.2
unnamed: C56.1, D134.2, R22.1, R156.1, R245.2
unnamed: C55.1, D133.2, R21.1, R157.1, R244.2
unnamed: C54.1, D132.2, R20.1, R158.1, R243.2
unnamed: C60.1, D138.2, R28.1, R160.1, R249.2
unnamed: C59.1, D137.2, R25.1, R161.1, R248.2
unnamed: C58.1, D136.2, R24.1, R162.1, R247.2
unnamed: C57.1, D135.2, R23.1, R163.1, R246.2
unnamed: R159.2, STAR_5.2
unnamed: R158.2, STAR_5.3
unnamed: R157.2, STAR_5.4
unnamed: R156.2, STAR_5.5
unnamed: R163.2, STAR_6.2
unnamed: R162.2, STAR_6.3
unnamed: R161.2, STAR_6.4
unnamed: R160.2, STAR_6.5
unnamed: R167.2, STAR_7.2
unnamed: R166.2, STAR_7.3
unnamed: R165.2, STAR_7.4
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
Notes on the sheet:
i2c 0x20
i2c 0x21
i2c 0x22
i2c 0x23
i2c 0x24
i2c 0x25
i2c 0x26
i2c 0x27
